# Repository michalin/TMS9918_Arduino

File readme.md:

# TMS9918_Arduino Library
## Arduino library for the TMS9918A, TMS9928A and TMS9929A Video Display processors.

The TMS9918 library is designed for Arduino Nano and Uno, wired to the VDP as shown in the the [schematic](/schematic/schematic.pdf). For different wiring or other platforms, adjust the *Core IO functions* in the [tms9918.cpp](src/tms9918.cpp) source file accordingly.

Copy all to the *library* folder of your Arduino IDE to install the library. Check out the [examples](/examples/readme.md).

## Watch video to learn more about the TMS9918.

## Build a TMS9918 based graphic card.

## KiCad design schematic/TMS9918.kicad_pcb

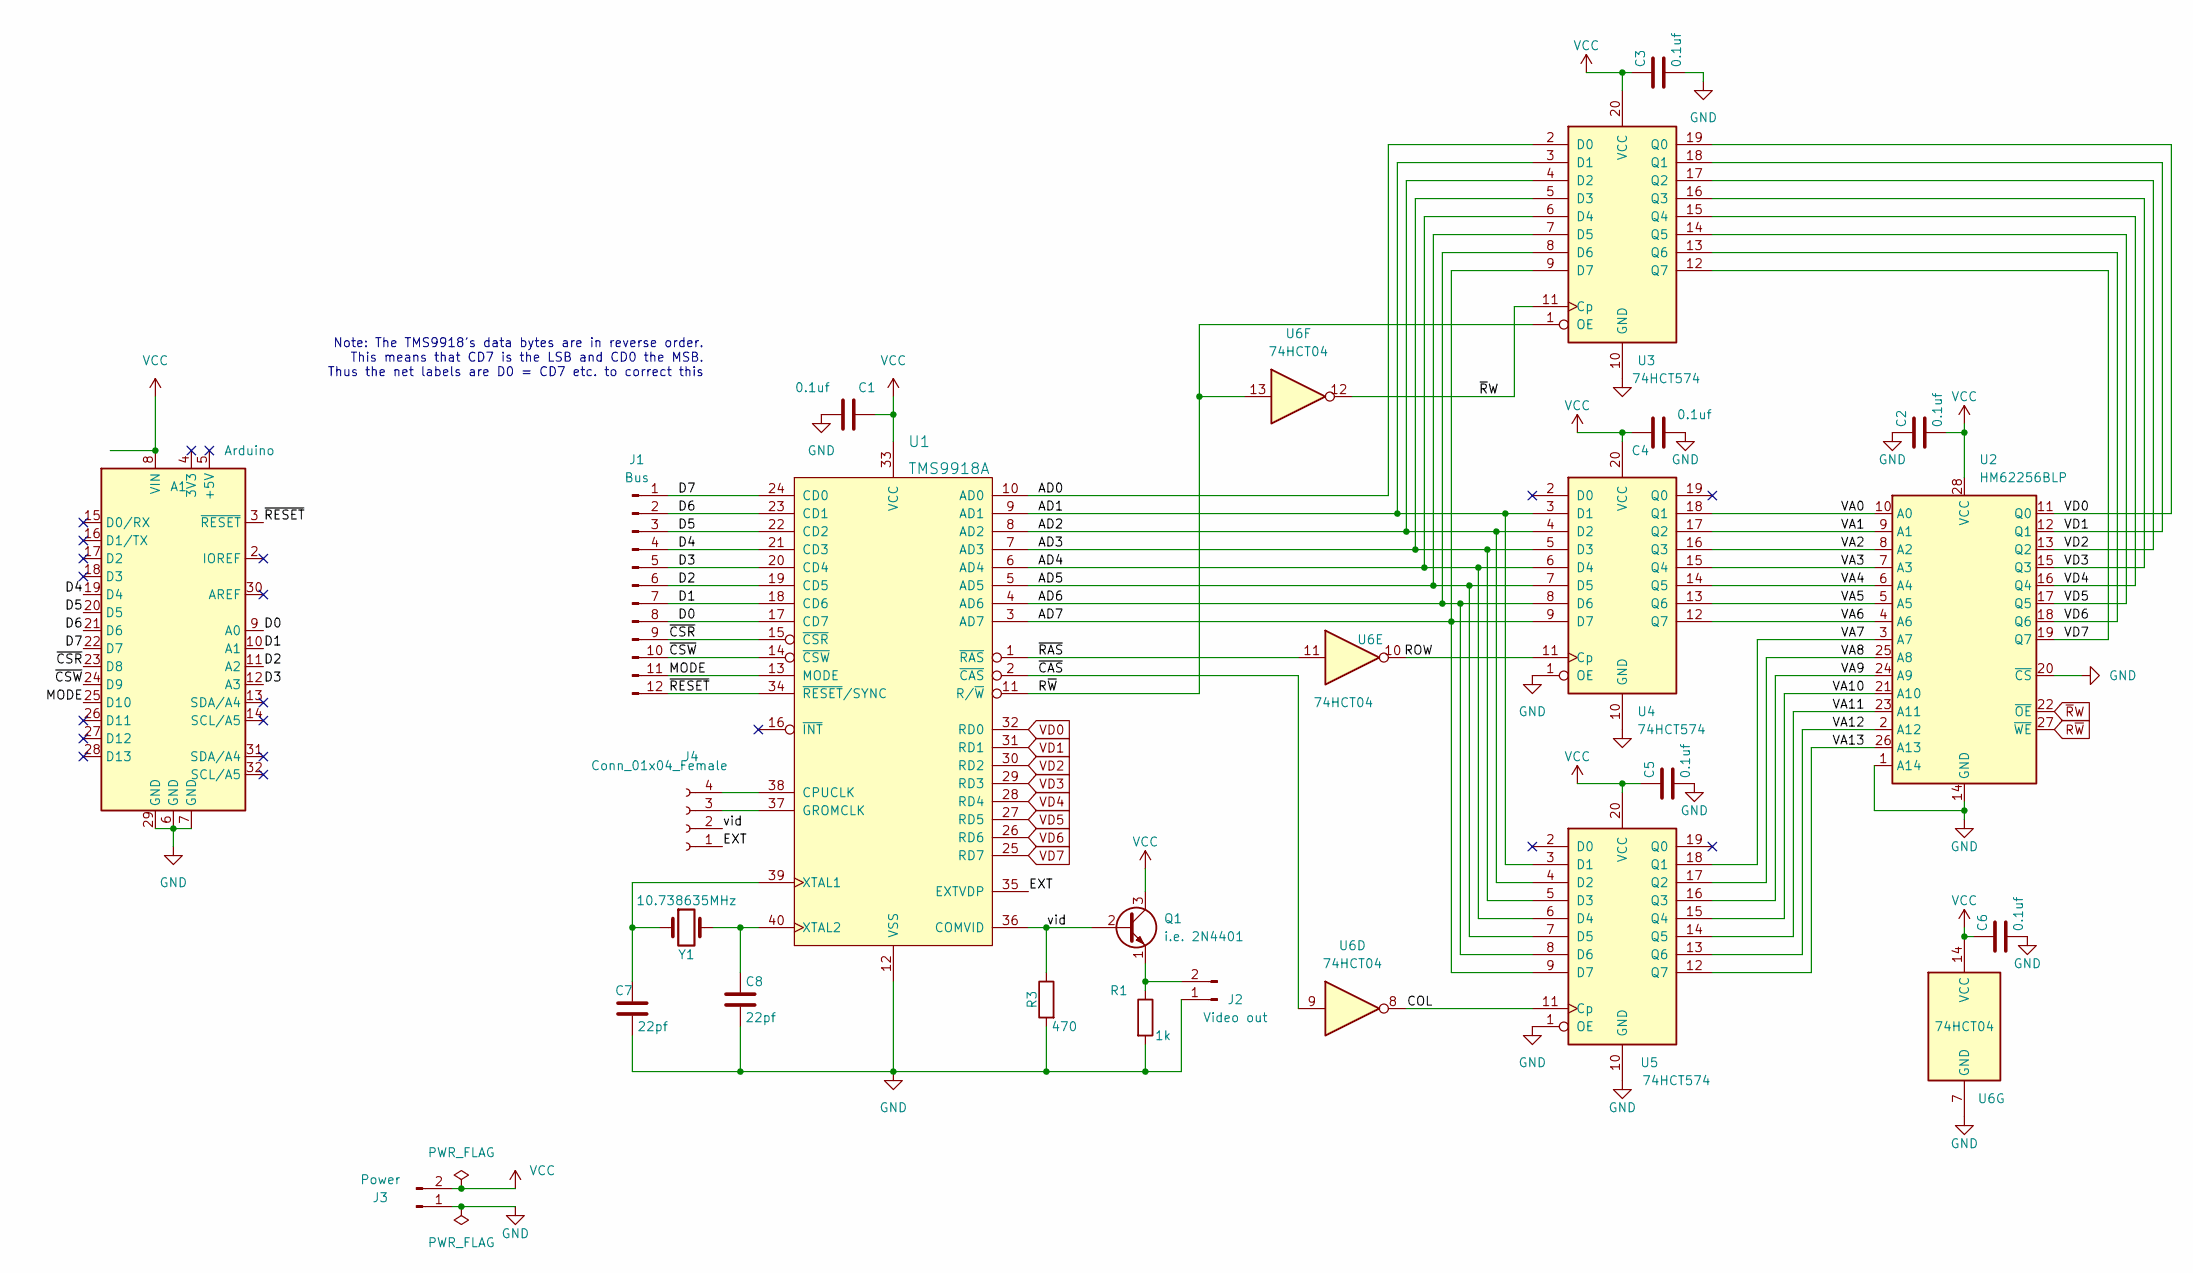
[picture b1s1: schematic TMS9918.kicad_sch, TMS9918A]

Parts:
A1: Arduino; Arduino_UNO_R3
C1, C2, C3, C4, C5, C6: 0.1uf; C_Disc_D3.0mm_W1.6mm_P2.50mm
C7, C8: 22pf; C_Disc_D3.0mm_W1.6mm_P2.50mm
J1: Bus; PinHeader_1x12_P2.54mm_Vertical
J2: Video out; PinHeader_1x02_P2.54mm_Horizontal
J3: Power; PinHeader_1x02_P2.54mm_Vertical
J4: Conn_01x04_Female; PinHeader_1x04_P2.54mm_Vertical
Q1: i.e. 2N4401; TO-92
R1: 1k; R_Axial_DIN0207_L6.3mm_D2.5mm_P7.62mm_Horizontal
R3: 470; R_Axial_DIN0207_L6.3mm_D2.5mm_P7.62mm_Horizontal
U1: TMS9918A; DIP-40_W15.24mm_Socket
U2: HM62256BLP; DIP-28_W15.24mm
U3, U4, U5: 74HCT574; DIP-20_W7.62mm_Socket
U6: 74HCT04; DIP-14_W7.62mm_Socket
Y1: 10.738635MHz; Crystal_HC49-4H_Vertical

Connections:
/AD0: U1.10 (AD0), U3.2 (D0)
/AD1: U1.9 (AD1), U3.3 (D1), U4.3 (D1), U5.3 (D1)
/AD2: U1.8 (AD2), U3.4 (D2), U4.4 (D2), U5.4 (D2)
/AD3: U1.7 (AD3), U3.5 (D3), U4.5 (D3), U5.5 (D3)
/AD4: U1.6 (AD4), U3.6 (D4), U4.6 (D4), U5.6 (D4)
/AD5: U1.5 (AD5), U3.7 (D5), U4.7 (D5), U5.7 (D5)
/AD6: U1.4 (AD6), U3.8 (D6), U4.8 (D6), U5.8 (D6)
/AD7: U1.3 (AD7), U3.9 (D7), U4.9 (D7), U5.9 (D7)
/COL: U5.11 (Cp), U6.8
/D0: A1.9 (A0), J1.8, U1.17 (CD7)
/D1: A1.10 (A1), J1.7, U1.18 (CD6)
/D2: A1.11 (A2), J1.6, U1.19 (CD5)
/D3: A1.12 (A3), J1.5, U1.20 (CD4)
/D4: A1.19 (D4), J1.4, U1.21 (CD3)
/D5: A1.20 (D5), J1.3, U1.22 (CD2)
/D6: A1.21 (D6), J1.2, U1.23 (CD1)
/D7: A1.22 (D7), J1.1, U1.24 (CD0)
/EXT: J4.1, U1.35 (EXTVDP)
/MODE: A1.25 (D10), J1.11, U1.13 (MODE)
/ROW: U4.11 (Cp), U6.10
/VA0: U2.10 (A0), U4.18 (Q1)
/VA1: U2.9 (A1), U4.17 (Q2)
/VA2: U2.8 (A2), U4.16 (Q3)
/VA3: U2.7 (A3), U4.15 (Q4)
/VA4: U2.6 (A4), U4.14 (Q5)
/VA5: U2.5 (A5), U4.13 (Q6)
/VA6: U2.4 (A6), U4.12 (Q7)
/VA7: U2.3 (A7), U5.18 (Q1)
/VA8: U2.25 (A8), U5.17 (Q2)
/VA9: U2.24 (A9), U5.16 (Q3)
/VA10: U2.21 (A10), U5.15 (Q4)
/VA11: U2.23 (A11), U5.14 (Q5)
/VA12: U2.2 (A12), U5.13 (Q6)
/VA13: U2.26 (A13), U5.12 (Q7)
/vid: J4.2, Q1.2 (B), R3.1, U1.36 (COMVID)
/~CAS: U1.2 (~CAS), U6.9
/~CSR: A1.23 (D8), J1.9, U1.15 (~CSR)
/~CSW: A1.24 (D9), J1.10, U1.14 (~CSW)
/~RAS: U1.1 (~RAS), U6.11
/~RESET: A1.3 (~RESET), J1.12, U1.34 (~RESET/SYNC)
GND: A1.6 (GND), A1.7 (GND), A1.29 (GND), C1.2, C2.1, C3.2, C4.2, C5.2, C6.2, C7.2, C8.2, J2.1, J3.1, R1.2, R3.2, U1.12 (VSS), U2.1 (A14), U2.14 (GND), U2.20 (~CS), U3.10 (GND), U4.1 (OE), U4.10 (GND), U5.1 (OE), U5.10 (GND), U6.7 (GND)
unnamed: C7.1, U1.39 (XTAL1), Y1.1
unnamed: C8.1, U1.40 (XTAL2), Y1.2
unnamed: J2.2, Q1.1 (E), R1.1
unnamed: J4.3, U1.37 (GROMCLK)
unnamed: J4.4, U1.38 (CPUCLK)
R~W: U1.11 (R/~W), U2.27 (~WE), U3.1 (OE), U6.13
VCC: A1.8 (VIN), C1.1, C2.2, C3.1, C4.1, C5.1, C6.1, J3.2, Q1.3 (C), U1.33 (VCC), U2.28 (VCC), U3.20 (VCC), U4.20 (VCC), U5.20 (VCC), U6.14 (VCC)
VD0: U1.32 (RD0), U2.11 (Q0), U3.19 (Q0)
VD1: U1.31 (RD1), U2.12 (Q1), U3.18 (Q1)
VD2: U1.30 (RD2), U2.13 (Q2), U3.17 (Q2)
VD3: U1.29 (RD3), U2.15 (Q3), U3.16 (Q3)
VD4: U1.28 (RD4), U2.16 (Q4), U3.15 (Q4)
VD5: U1.27 (RD5), U2.17 (Q5), U3.14 (Q5)
VD6: U1.26 (RD6), U2.18 (Q6), U3.13 (Q6)
VD7: U1.25 (RD7), U2.19 (Q7), U3.12 (Q7)
~RW: U2.22 (~OE), U3.11 (Cp), U6.12

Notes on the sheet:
Note: The TMS9918's data bytes are in reverse order. This means that CD7 is the LSB and CD0 the MSB. Thus the net labels are D0 = CD7 etc. to correct this

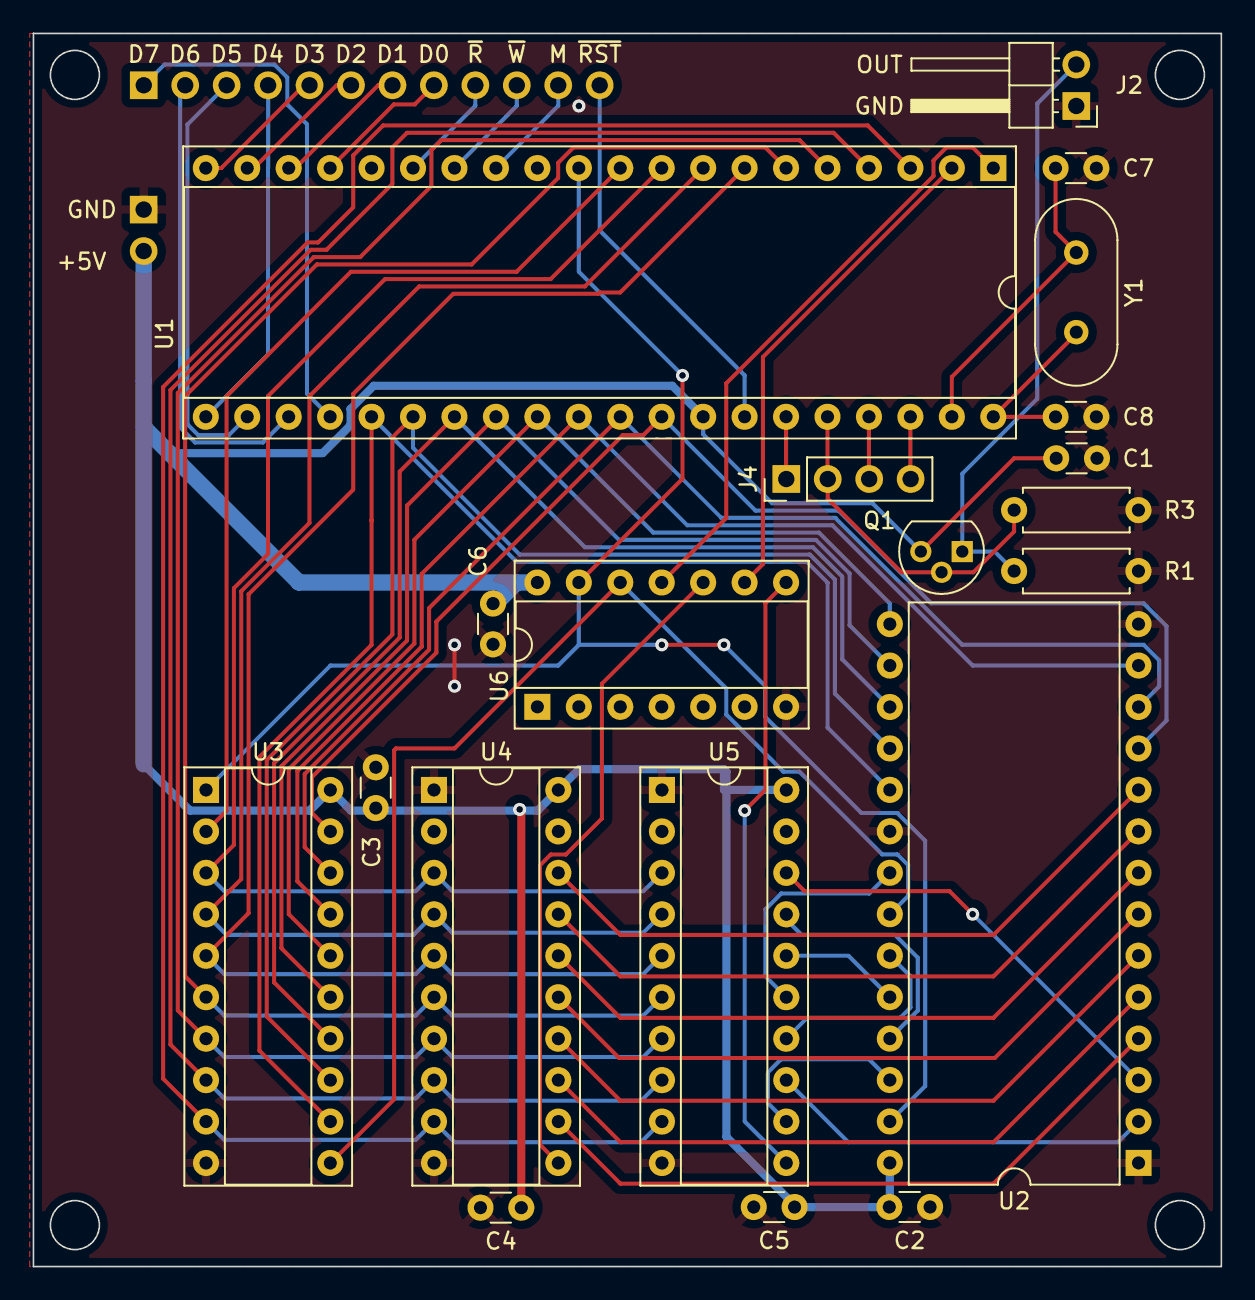
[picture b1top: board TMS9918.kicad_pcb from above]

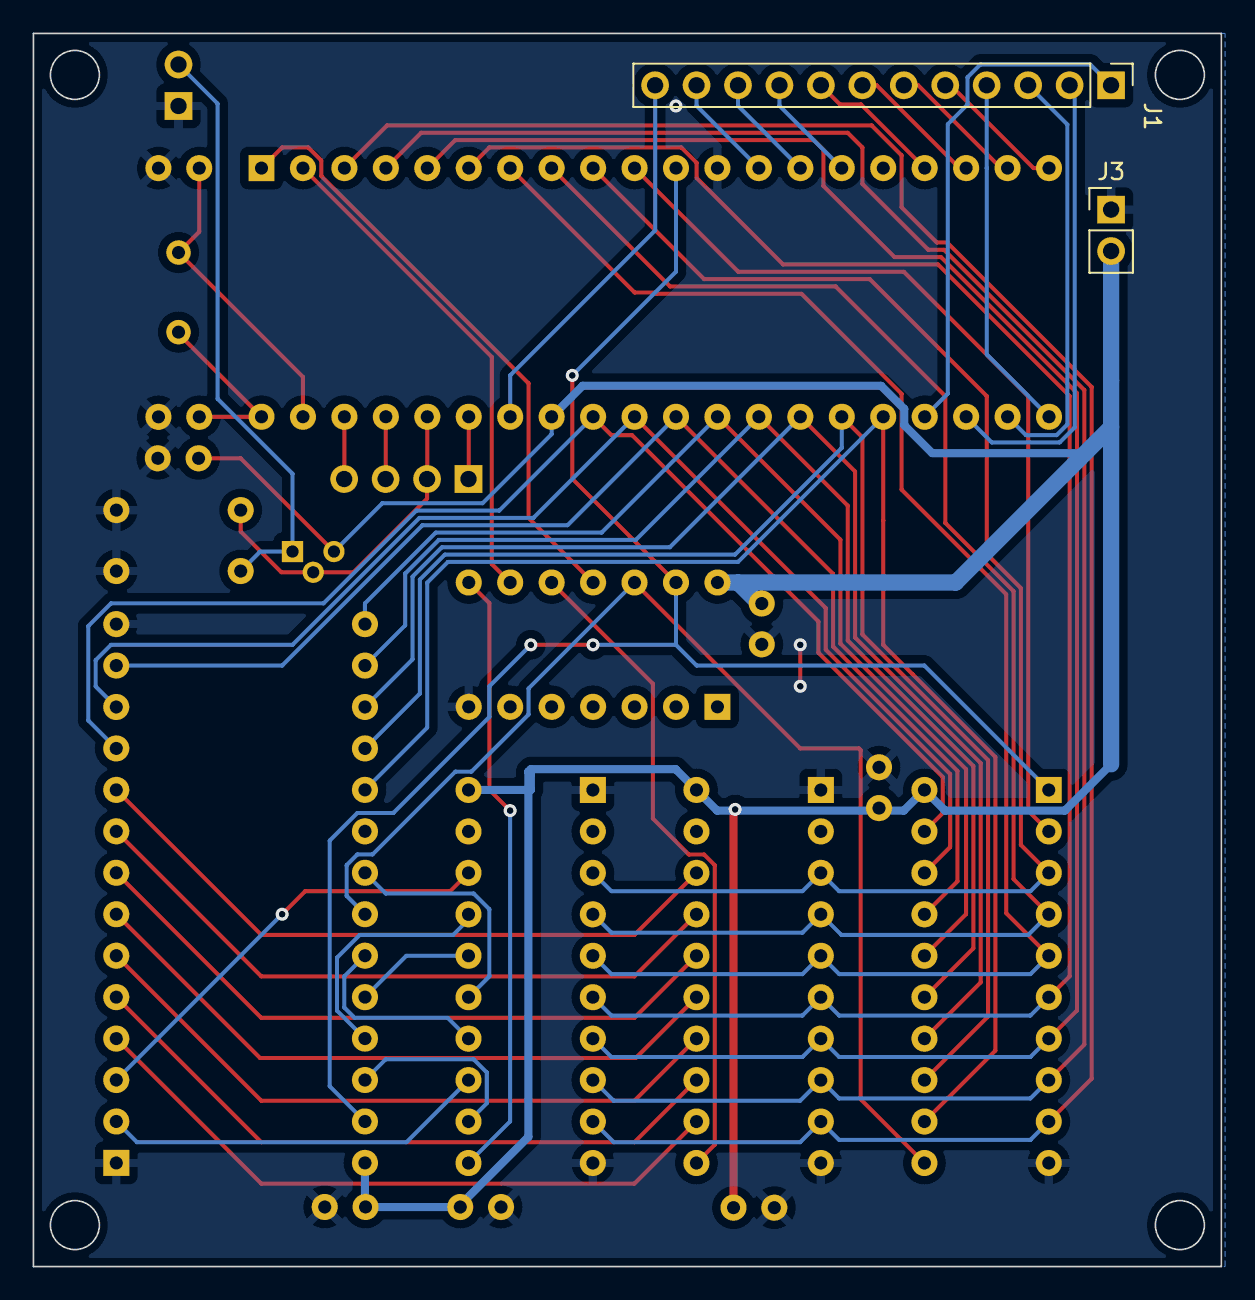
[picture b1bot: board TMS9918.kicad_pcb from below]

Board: 2 copper layers, 72.8 x 75.6 mm, 22 parts (2 on the bottom side), 57 nets.

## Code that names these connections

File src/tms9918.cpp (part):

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#include "patterns.h"

#define MODE 11
#define CSW 10
#define CSR 9
#define RESET 8
#define R1_IE 0x20
#define R1_M1 0x10
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    sprite_size_sel = big_sprites;
    pinMode(MODE, OUTPUT);
    pinMode(RESET, OUTPUT);
    pinMode(CSW, OUTPUT);
    pinMode(CSR, OUTPUT);

    digitalWrite(RESET, HIGH);
    digitalWrite(MODE, HIGH);
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    }
    else if (col > crsr_max_x)
    {
        col = 0;
        row++;
    }

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    }
    else if (row > crsr_max_y)
    {
        row = 0;
    }

    cursor.x = col;
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
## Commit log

2022-03-27 Version 1.0.0
2022-04-30 V1.1
    Various improvements
2022-05-01 V1.1
2022-05-01 V1.1
    Instructions on how to create raw image files for the imgserial tool
2022-05-02 V1.2
    Silkscreen updated
2022-05-02 V1.2
    Label D0..D7 order changed
2022-05-16 V1.2
    Wiring error Pin 8-11 between Arduino and module fixed
2022-06-25 Soldermasks added
2023-12-25 PR: Fix identical instruction for conditional sprite_size_sel @ function vdp_sprite_init
    Fixes name attribution for size 0 sprites (8x8 sprites) @ function vdp_sprite_init

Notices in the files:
src/tms9918.cpp:
Copyright (C) 2022  Doctor Volt
This program is free software: you can redistribute it and/or modify
it under the terms of the GNU General Public License as published by
the Free Software Foundation, either version 3 of the License, or
(at your option) any later version.
